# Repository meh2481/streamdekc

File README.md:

# streamdekc
Like a streamdeck, but homemade and worse!

# Materials
Parts used:
- 8x [I2C OLED Displays](https://smile.amazon.com/dp/B09C5K91H7)
- 8x [Tactile push buttons](https://www.ebay.com/itm/303314070463)
- 4x [10K slide pots](https://smile.amazon.com/dp/B08C7C4PL3)
- 1x [QT Py 2040](https://www.adafruit.com/product/4900)
- 2x [74HC4051P Mux/Demux](https://smile.amazon.com/dp/B016G4MQH8)

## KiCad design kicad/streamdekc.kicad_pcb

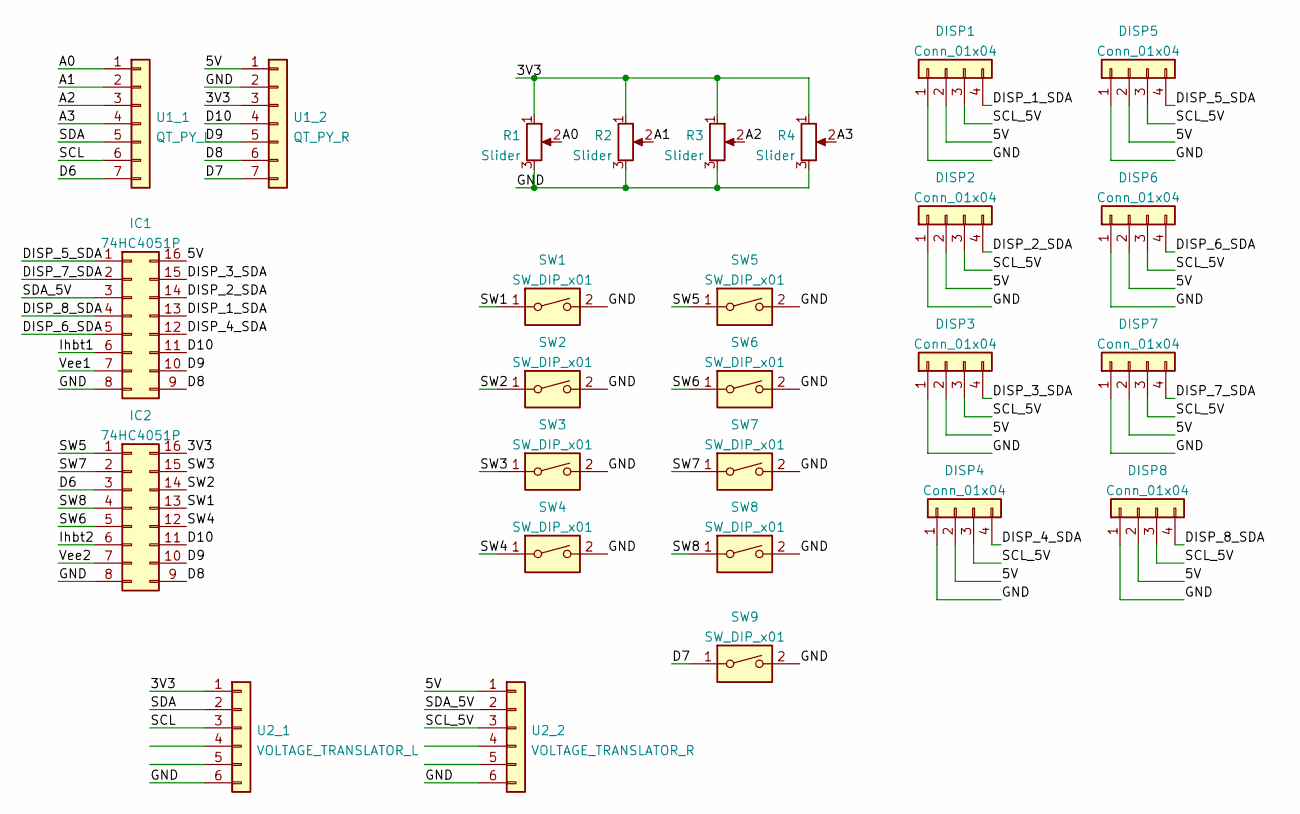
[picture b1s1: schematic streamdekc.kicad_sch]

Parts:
DISP1, DISP2, DISP3, DISP4, DISP5, DISP6, DISP7, DISP8: Conn_01x04; PinHeader_1x04_P2.54mm_Vertical
IC1, IC2: 74HC4051P; DIP-16_W7.62mm_LongPads
R1, R2, R3, R4: Slider; Potentiometer_Bourns_PTA3043_Single_Slide
SW1, SW2, SW3, SW4, SW5, SW6, SW7, SW8: SW_DIP_x01; Switch_2pin_6mm_p4.5mm
SW9: SW_DIP_x01; PinHeader_1x02_P2.54mm_Vertical
U1_1: QT_PY_L; PinHeader_1x07_P2.54mm_Vertical
U1_2: QT_PY_R; PinHeader_1x07_P2.54mm_Vertical
U2_1: VOLTAGE_TRANSLATOR_L; PinHeader_1x06_P2.54mm_Vertical
U2_2: VOLTAGE_TRANSLATOR_R; PinHeader_1x06_P2.54mm_Vertical

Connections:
/3V3: IC2.16, R1.1, R2.1, R3.1, R4.1, U1_2.3, U2_1.1
/5V: DISP1.2, DISP2.2, DISP3.2, DISP4.2, DISP5.2, DISP6.2, DISP7.2, DISP8.2, IC1.16, U1_2.1, U2_2.1
/A0: R1.2, U1_1.1
/A1: R2.2, U1_1.2
/A2: R3.2, U1_1.3
/A3: R4.2, U1_1.4
/D6: IC2.3, U1_1.7
/D7: SW9.1, U1_2.7
/D8: IC1.9, IC2.9, U1_2.6
/D9: IC1.10, IC2.10, U1_2.5
/D10: IC1.11, IC2.11, U1_2.4
/DISP_1_SDA: DISP1.4, IC1.13
/DISP_2_SDA: DISP2.4, IC1.14
/DISP_3_SDA: DISP3.4, IC1.15
/DISP_4_SDA: DISP4.4, IC1.12
/DISP_5_SDA: DISP5.4, IC1.1
/DISP_6_SDA: DISP6.4, IC1.5
/DISP_7_SDA: DISP7.4, IC1.2
/DISP_8_SDA: DISP8.4, IC1.4
/GND: DISP1.1, DISP2.1, DISP3.1, DISP4.1, DISP5.1, DISP6.1, DISP7.1, DISP8.1, IC1.8, IC2.8, R1.3, R2.3, R3.3, R4.3, SW1.2, SW2.2, SW3.2, SW4.2, SW5.2, SW6.2, SW7.2, SW8.2, SW9.2, U1_2.2, U2_1.6, U2_2.6
/Ihbt1: IC1.6
/Ihbt2: IC2.6
/SCL: U1_1.6, U2_1.3
/SCL_5V: DISP1.3, DISP2.3, DISP3.3, DISP4.3, DISP5.3, DISP6.3, DISP7.3, DISP8.3, U2_2.3
/SDA: U1_1.5, U2_1.2
/SDA_5V: IC1.3, U2_2.2
/SW1: IC2.13, SW1.1
/SW2: IC2.14, SW2.1
/SW3: IC2.15, SW3.1
/SW4: IC2.12, SW4.1
/SW5: IC2.1, SW5.1
/SW6: IC2.5, SW6.1
/SW7: IC2.2, SW7.1
/SW8: IC2.4, SW8.1
/Vee1: IC1.7
/Vee2: IC2.7

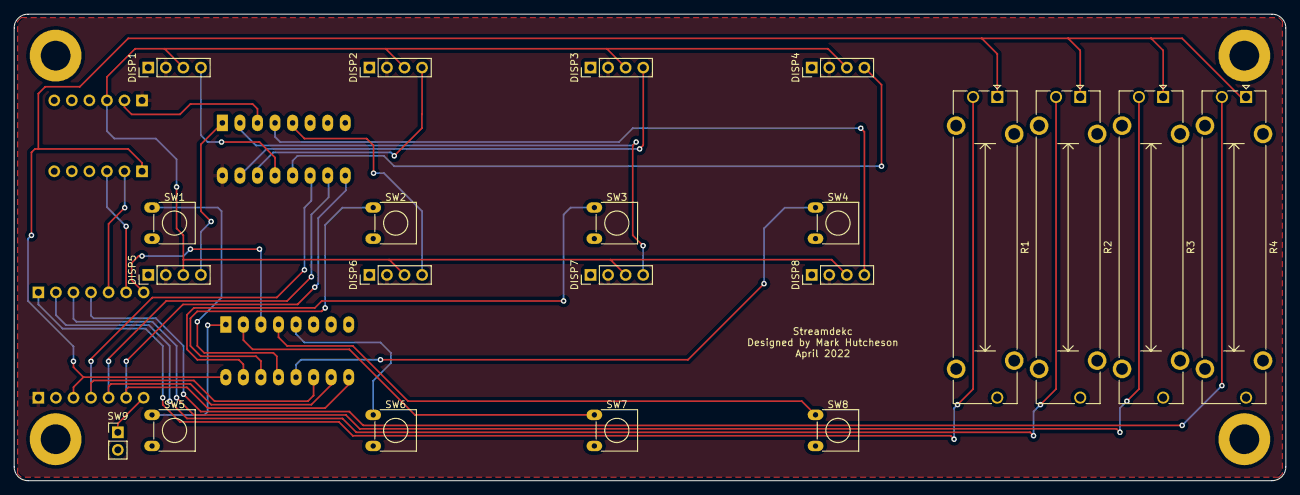
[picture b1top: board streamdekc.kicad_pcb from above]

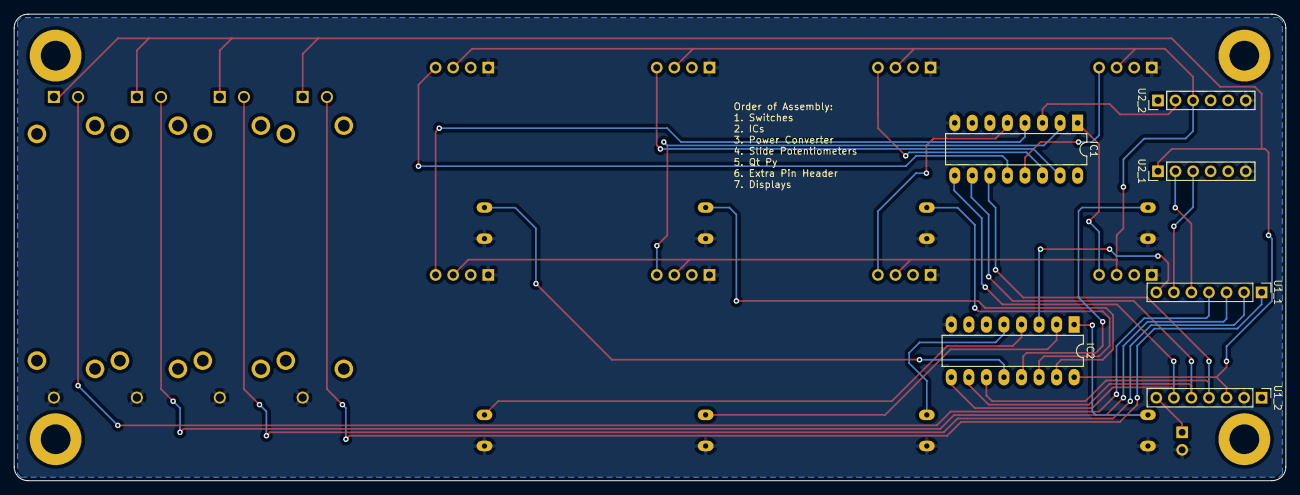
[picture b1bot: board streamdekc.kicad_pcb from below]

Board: 2 copper layers, 184.0 x 67.5 mm, 27 parts (6 on the bottom side), 32 nets.

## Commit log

2022-04-14 draw to display
2022-04-14 Initial test of 2 displays at once
2022-04-14 Add TODO
2022-04-14 Add initial BOM
2022-04-14 Trying 5V logic, scanlines off on display 1
2022-04-14 Fix terminal out breaking display 1
2022-04-14 hey nice it actually works
2022-04-18 add slider potentiometer
2022-04-18 Add KiCad files
2022-04-18 whee
2022-04-19 Initial pcb design
2022-04-19 Move QtPy for easier (aka physically possible) assembly
2022-04-19 Gen gerber files
2022-05-07 Add FreeCAD and stl files
2022-05-07 Move folder to more proper name
2022-05-08 Giving up on this project for now; I2C hardware problems, case needs redesign
